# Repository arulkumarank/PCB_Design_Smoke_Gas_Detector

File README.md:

View this project on [CADLAB.io](https://cadlab.io/project/29098). 

# PCB_Design_Smoke_Gas_Detector

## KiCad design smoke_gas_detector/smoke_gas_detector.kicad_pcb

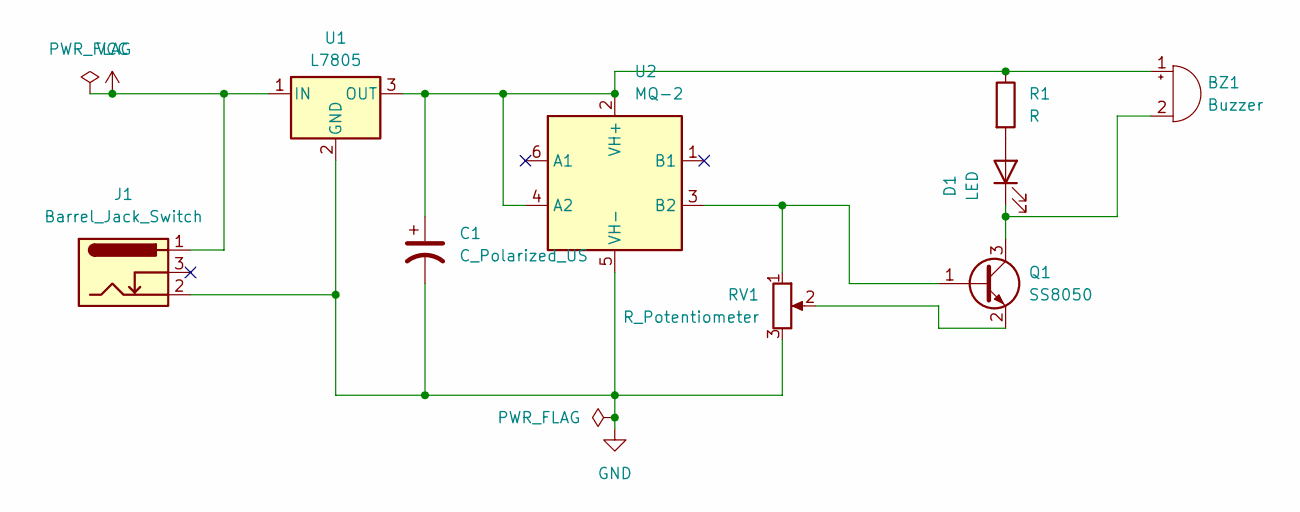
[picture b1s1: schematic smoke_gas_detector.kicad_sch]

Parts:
BZ1: Buzzer; Buzzer_12x9.5RM7.6
C1: C_Polarized_US; CP_Axial_L10.0mm_D4.5mm_P15.00mm_Horizontal
D1: LED; LED_0805_2012Metric_Pad1.15x1.40mm_HandSolder
J1: Barrel_Jack_Switch; BarrelJack_CLIFF_FC681465S_SMT_Horizontal
Q1: SS8050; SOT-23
R1: R; R_0612_1632Metric_Pad1.18x3.40mm_HandSolder
RV1: R_Potentiometer; Potentiometer_ACP_CA6-H2,5_Horizontal
U1: L7805; TO-252-2
U2: MQ-2; MQ-6

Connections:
GND: C1.2, J1.2, RV1.3, U1.2 (GND), U2.5 (VH-)
unnamed: BZ1.1 (+), C1.1, R1.1, U1.3 (OUT), U2.2 (VH+), U2.4 (A2)
unnamed: BZ1.2 (-), D1.1 (K), Q1.3 (C)
unnamed: D1.2 (A), R1.2
unnamed: Q1.1 (B), RV1.1, U2.3 (B2)
unnamed: Q1.2 (E), RV1.2
VCC: J1.1, U1.1 (IN)

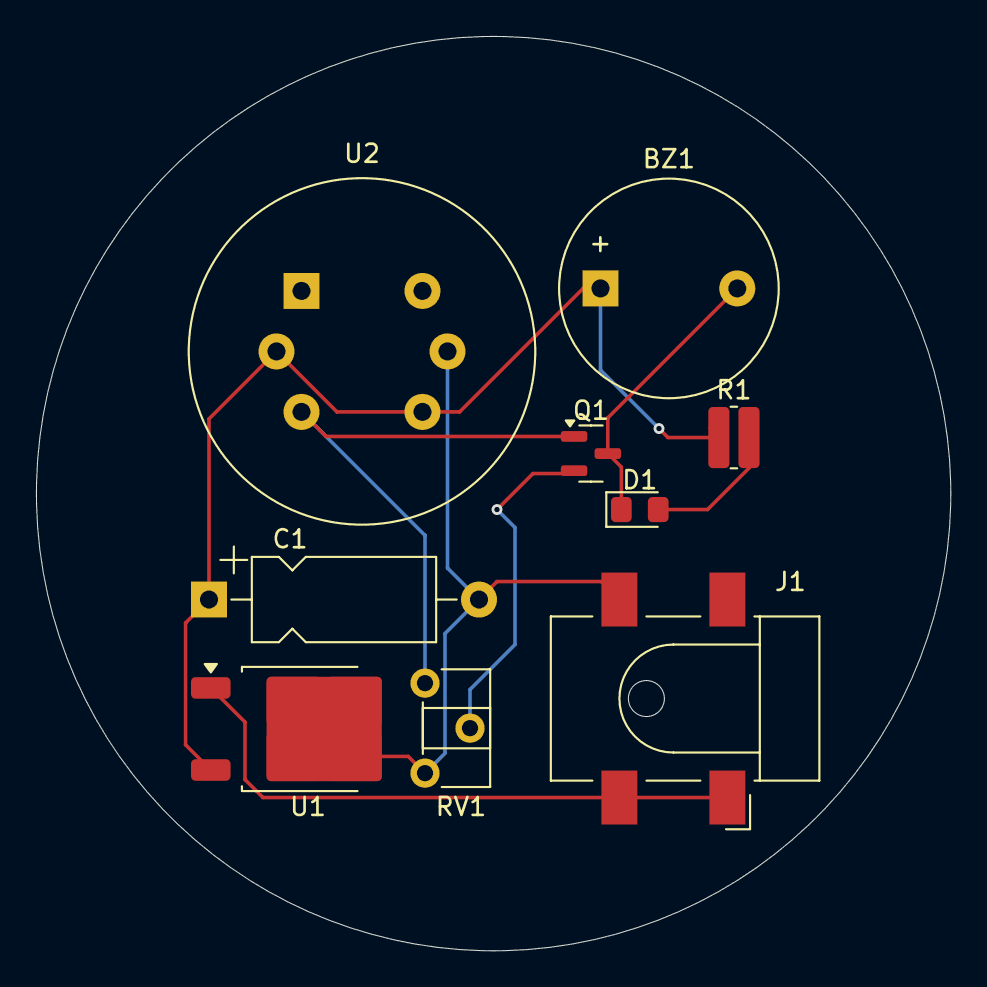
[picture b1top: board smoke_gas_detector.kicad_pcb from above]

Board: 2 copper layers, 50.8 x 50.8 mm, 9 parts (0 on the bottom side), 7 nets.

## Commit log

2025-03-31 Smoke Gas Detector PCB Design
2025-03-31 Backlink to CADLAB.io has been added.
2025-04-02 Smoke Gas Detector
